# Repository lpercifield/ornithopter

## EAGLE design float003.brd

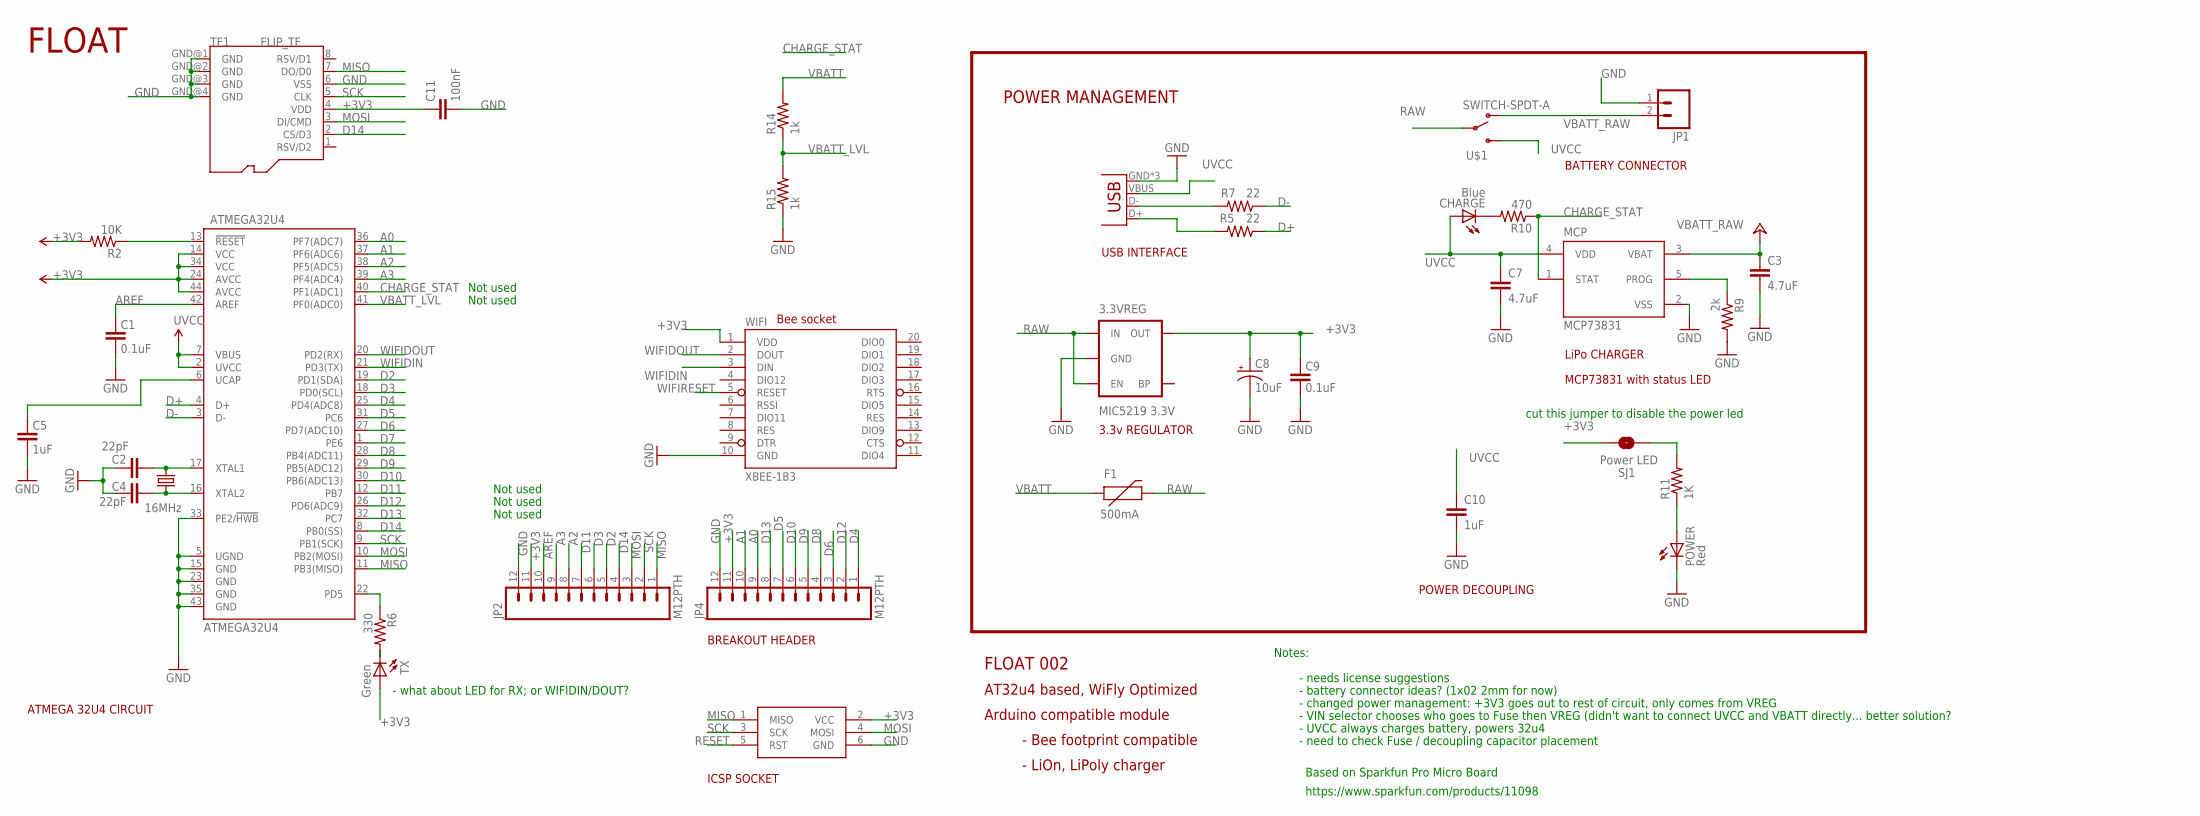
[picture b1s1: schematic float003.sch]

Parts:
3.3VREG: MIC5219 3.3V; SOT23-5
ATMEGA32U4: ATMEGA32U4; QFN-44-NOPAD
C1, C9: 0.1uF; 0402-CAP
C2, C4: 22pF; 0402-CAP
C3, C7: 4.7uF; 0402-CAP
C5, C10: 1uF; 0402-CAP
C8: 10uF; EIA3216
C11: 100nF; 0402-CAP
CHARGE: Blue; LED-0603
F1: 500mA; PTC-1206
ISP1: AVRISP-6; AVRISP
JP1: M02JST-PTH-2; JST-2-PTH
JP2, JP4: M12PTH; 1X12
MCP: MCP73831; SOT23-5
POWER: Red; LED-0603
R2: 10K; 0402-RES
R5, R7: 22; 0402-RES
R6: 330; 0402-RES
R9: 2k; 0402-RES
R10: 470; 0402-RES
R11: 1K; 0402-RES
R14, R15: 1k; 0402-RES
SJ1: Power LED; SJ_2S-TRACE
TF1: FLIP_TF
TX: Green; LED-0603
U$1: SWITCH-SPDT-A
WIFI: XBEE-1B3; XBEE-SMD
X2: USB-MICROB
Y1: 16MHz; CRYSTAL-SMD-5X3

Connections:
+3V3: 3.3VREG.5 (OUT), ATMEGA32U4.14 (VCC), ATMEGA32U4.24 (AVCC), ATMEGA32U4.34 (VCC), ATMEGA32U4.44 (AVCC), C8.A (+), C9.2, C11.1, ISP1.2 (VCC), JP2.11, JP4.11, R2.2, SJ1.2, TF1.4 (VDD), TX.A, WIFI.1 (VDD)
A0: ATMEGA32U4.36 (PF7(ADC7)), JP4.9
A1: ATMEGA32U4.37 (PF6(ADC6)), JP4.10
A2: ATMEGA32U4.38 (PF5(ADC5)), JP2.8
A3: ATMEGA32U4.39 (PF4(ADC4)), JP2.9
AREF: ATMEGA32U4.42 (AREF), C1.2, JP2.10
CHARGE_STAT: ATMEGA32U4.40 (PF1(ADC1)), MCP.1 (STAT), R10.1
D2: ATMEGA32U4.19 (PD1(SDA)), JP2.5
D3: ATMEGA32U4.18 (PD0(SCL)), JP2.6
D4: ATMEGA32U4.25 (PD4(ADC8)), JP4.1
D5: ATMEGA32U4.31 (PC6), JP4.7
D6: ATMEGA32U4.27 (PD7(ADC10)), JP4.3
D7: ATMEGA32U4.1 (PE6)
D8: ATMEGA32U4.28 (PB4(ADC11)), JP4.4
D9: ATMEGA32U4.29 (PB5(ADC12)), JP4.5
D10: ATMEGA32U4.30 (PB6(ADC13)), JP4.6
D11: ATMEGA32U4.12 (PB7), JP2.7
D12: ATMEGA32U4.26 (PD6(ADC9)), JP4.2
D13: ATMEGA32U4.32 (PC7), JP4.8
D14: ATMEGA32U4.8 (PB0(SS)), JP2.4, TF1.2 (CS/D3)
D+: ATMEGA32U4.4 (D+), R5.1
D-: ATMEGA32U4.3 (D-), R7.1
GND: 3.3VREG.2 (GND), ATMEGA32U4.5 (UGND), ATMEGA32U4.15 (GND), ATMEGA32U4.23 (GND), ATMEGA32U4.33 (PE2/!HWB), ATMEGA32U4.35 (GND), ATMEGA32U4.43 (GND), C1.1, C2.2, C3.2, C4.2, C5.1, C7.2, C8.C (-), C9.1, C10.2, C11.2, ISP1.6 (GND), JP1.1, JP2.12, JP4.12, MCP.2 (VSS), POWER.C, R9.2, R15.1, TF1.6 (VSS), TF1.GND@1 (GND), TF1.GND@2 (GND), TF1.GND@3 (GND), TF1.GND@4 (GND), WIFI.10 (GND), X2.GND, X2.MT1 (GND), X2.MT2 (GND)
MISO: ATMEGA32U4.11 (PB3(MISO)), ISP1.1 (MISO), JP2.1, TF1.7 (DO/D0)
MOSI: ATMEGA32U4.10 (PB2(MOSI)), ISP1.4 (MOSI), JP2.3, TF1.3 (DI/CMD)
unnamed: ATMEGA32U4.16 (XTAL2), C4.1, Y1.1
unnamed: ATMEGA32U4.17 (XTAL1), C2.1, Y1.3 (2)
unnamed: CHARGE.C, R10.2
unnamed: ATMEGA32U4.6 (UCAP), C5.2
unnamed: R7.2, X2.D-
unnamed: R6.2, TX.C
unnamed: R5.2, X2.D+
unnamed: MCP.5 (PROG), R9.1
unnamed: R11.2, SJ1.1
unnamed: POWER.A, R11.1
RAW: 3.3VREG.1 (IN), 3.3VREG.3 (EN), F1.2, U$1.2
RESET: ATMEGA32U4.13 (!RESET), ISP1.5 (RST), R2.1
SCK: ATMEGA32U4.9 (PB1(SCK)), ISP1.3 (SCK), JP2.2, TF1.5 (CLK)
TXLED: ATMEGA32U4.22 (PD5), R6.1
UVCC: ATMEGA32U4.2 (UVCC), ATMEGA32U4.7 (VBUS), C7.1, C10.1, CHARGE.A, MCP.4 (VDD), U$1.1 (S), X2.VBUS
VBATT: F1.1, R14.2
VBATT_LVL: ATMEGA32U4.41 (PF0(ADC0)), R14.1, R15.2
VBATT_RAW: C3.1, JP1.2, MCP.3 (VBAT), U$1.3 (O)
WIFIDIN: ATMEGA32U4.21 (PD3(TX)), WIFI.3 (DIN)
WIFIDOUT: ATMEGA32U4.20 (PD2(RX)), WIFI.2 (DOUT)
WIFIRESET: WIFI.5 (RESET)

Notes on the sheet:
Not used
Based on Sparkfun Pro Micro Board
https://www.sparkfun.com/products/11098
USB INTERFACE
ICSP SOCKET
3.3v REGULATOR
POWER DECOUPLING
ATMEGA 32U4 CIRCUIT
BREAKOUT HEADER
Bee socket
LiPo CHARGER
POWER MANAGEMENT
FLOAT
Notes:
- needs license suggestions
- battery connector ideas? (1x02 2mm for now)
- changed power management: +3V3 goes out to rest of circuit, only comes from VREG
FLOAT 002
AT32u4 based, WiFly Optimized
- Bee footprint compatible
- LiOn, LiPoly charger
BATTERY CONNECTOR
Arduino compatible module
- UVCC always charges battery, powers 32u4
- VIN selector chooses who goes to Fuse then VREG (didn't want to connect UVCC and VBATT directly... better solution?
- need to check Fuse / decoupling capacitor placement
- what about LED for RX; or WIFIDIN/DOUT?
MCP73831 with status LED
cut this jumper to disable the power led

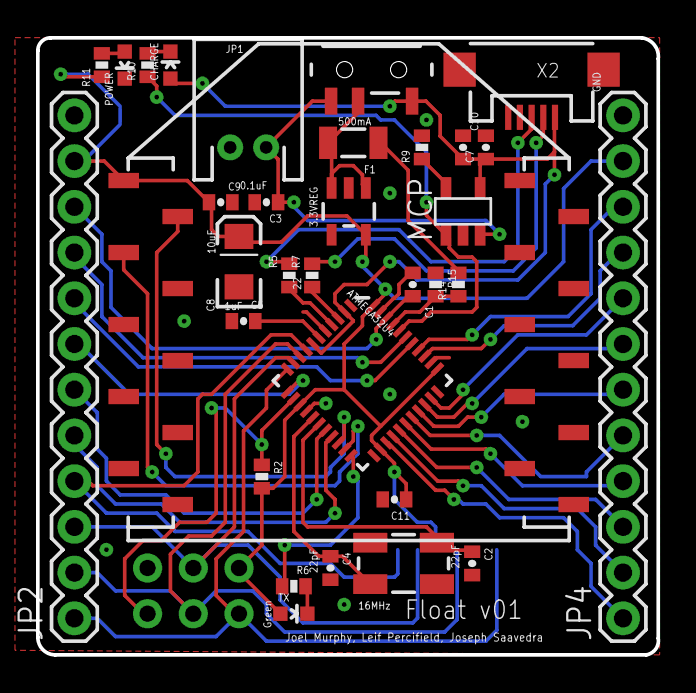
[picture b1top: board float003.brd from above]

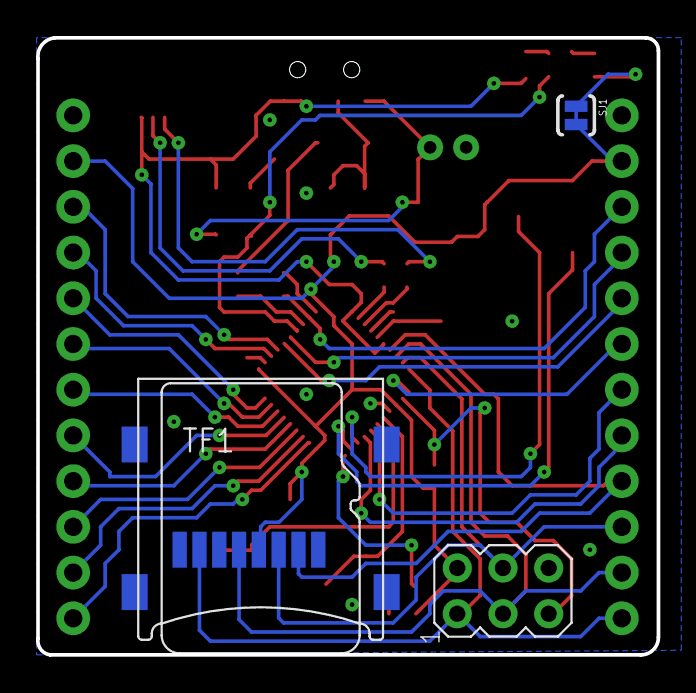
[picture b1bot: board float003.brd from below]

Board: 2 copper layers, 34.5 x 34.3 mm, 36 parts (3 on the bottom side), 44 nets.

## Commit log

2013-05-04 added lipo + battery, changed name to Float002
2013-05-04 added notes to schematic, BOM.txt
2013-05-04 more notes
2013-05-04 added .gitignore
2013-05-04 board v 2
2013-05-05 added float v3
2013-05-07 added switch and microsd card
2013-06-10 updated float v3

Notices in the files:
parts and their libraries:
SparkFun-DigitalIC: Licensing: CC v3.0 Share-Alike You are welcome to use this library for commercial purposes.
